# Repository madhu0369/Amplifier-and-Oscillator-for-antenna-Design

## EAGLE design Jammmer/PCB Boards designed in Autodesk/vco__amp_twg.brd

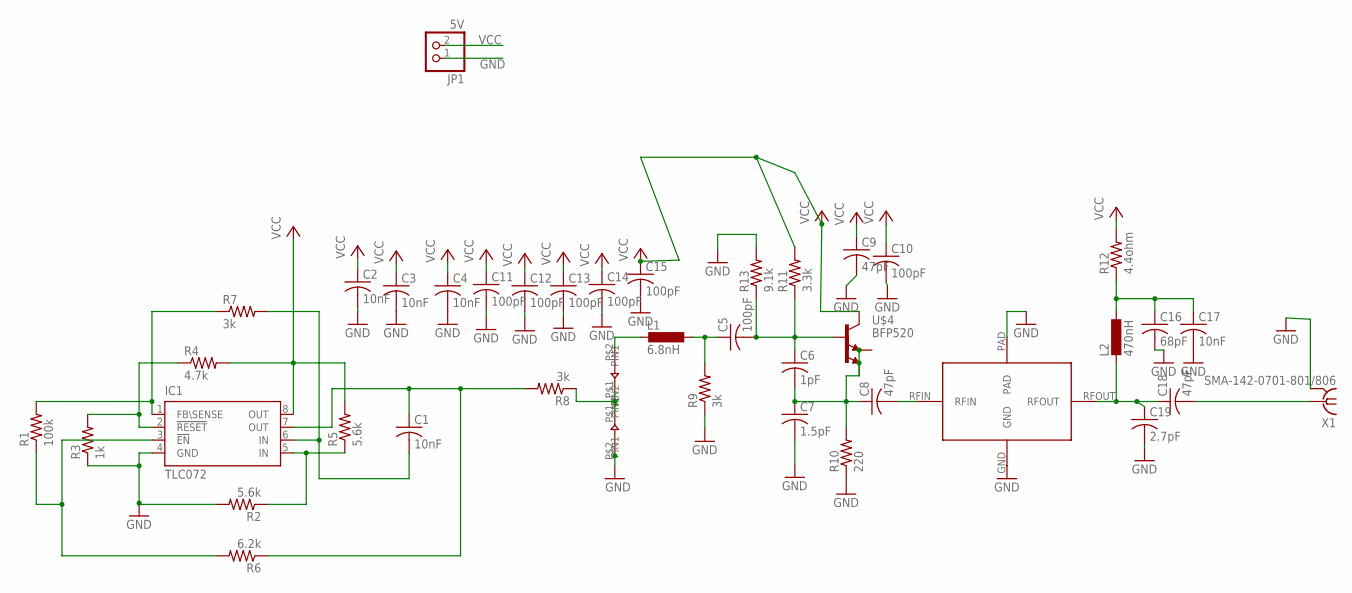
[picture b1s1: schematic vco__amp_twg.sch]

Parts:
C1, C2, C3, C4, C17: 10nF; C0603
C5, C10, C11, C12, C13, C14, C15: 100pF; C0603
C6: 1pF; C0603
C7: 1.5pF; C0603
C8, C9, C18: 47pF; C0603
C16: 68pF; C0603
C19: 2.7pF; C0603
IC1: TLC072; SOP-08
JP1: 5V; 1X02
L1: 6.8nH; L0603
L2: 470nH; L0603
R1: 100k; R0603
R2, R5: 5.6k; R0603
R3: 1k; R0603
R4: 4.7k; R0603
R6: 6.2k; R0603
R7, R8, R9: 3k; R0603
R10: 220; R0603
R11: 3.3k; R0603
R12: 4.4ohm; R0603
R13: 9.1k; R0603
U$1, U$5: BBY5702
U$2: MMG3001; SOT-89
U$4: BFP520; SOT343
X1: SMA-142-0701-801/806; J502-ND-142-0701-801/806

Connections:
GND: C2.2, C3.2, C4.2, C7.2, C9.2, C10.2, C11.2, C12.2, C13.2, C14.2, C15.2, C16.2, C17.2, C19.2, IC1.4 (GND), JP1.1, R2.2, R3.1, R9.1, R10.1, R13.2, U$2.GND, U$2.PAD, U$5.P$2 (PIN2), X1.G@1 (2), X1.G@2 (2), X1.G@3 (2), X1.G@4 (2)
unnamed: IC1.1 (FB\SENSE), R1.2, R7.1
unnamed: IC1.3 (!EN), R1.1, R6.2
unnamed: C8.2, U$2.RFIN
unnamed: IC1.5 (IN), R2.1, R5.1
unnamed: IC1.2 (!RESET), R3.2, R4.1
unnamed: L1.2, U$1.P$2 (PIN2)
unnamed: C1.1, IC1.7 (OUT), R6.1, R8.2
unnamed: C1.2, IC1.6 (IN), R7.2
unnamed: C5.1, L1.1, R9.2
unnamed: C16.1, C17.1, L2.1, R12.1
unnamed: C5.2, C6.1, R11.1, R13.1, U$4.1 (B)
unnamed: R8.1, U$1.P$1 (PIN1), U$5.P$1 (PIN1)
unnamed: C18.1, C19.1, L2.2, U$2.RFOUT
unnamed: C18.2, X1.1
unnamed: C6.2, C7.1, C8.1, R10.2, U$4.2 (E1), U$4.4 (E2)
VCC: C2.1, C3.1, C4.1, C9.1, C10.1, C11.1, C12.1, C13.1, C14.1, C15.1, IC1.8 (OUT), JP1.2, R4.2, R5.2, R11.2, R12.2, U$4.3 (C)

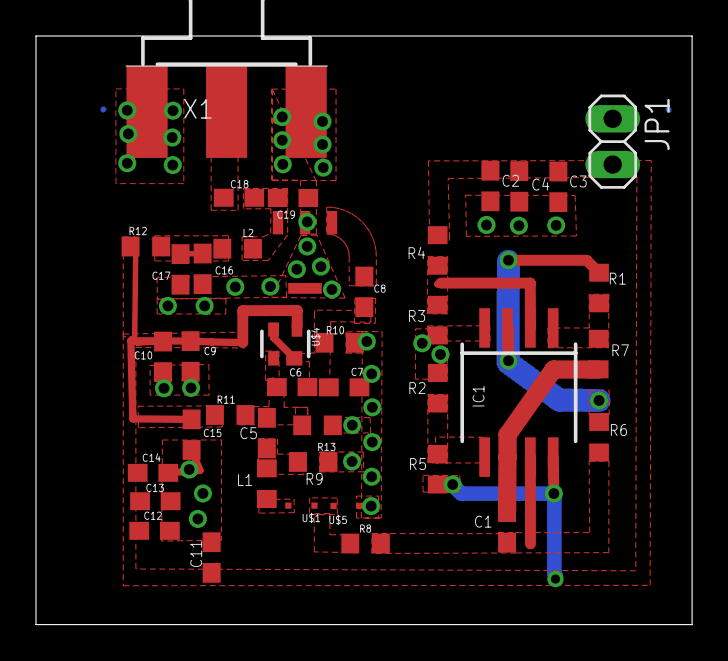
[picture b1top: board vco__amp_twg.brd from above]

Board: 2 copper layers, 36.5 x 32.7 mm, 41 parts (0 on the bottom side), 17 nets.
